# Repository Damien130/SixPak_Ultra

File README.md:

# SixPak_Ultra
- Currently in Alpha

A combination expansion card for the XT Bus, contains
  
  High speed Intel 16550 UART
  
  SVGA Controller
  
  Ethernet Controller
  
  AdLib compatible sound card
  
  Real Time Clock
  
  Floppy Controller with 3.5 Inch HD diskette support
  
This is a spiritual successor of AST's SixPak Plus ;)

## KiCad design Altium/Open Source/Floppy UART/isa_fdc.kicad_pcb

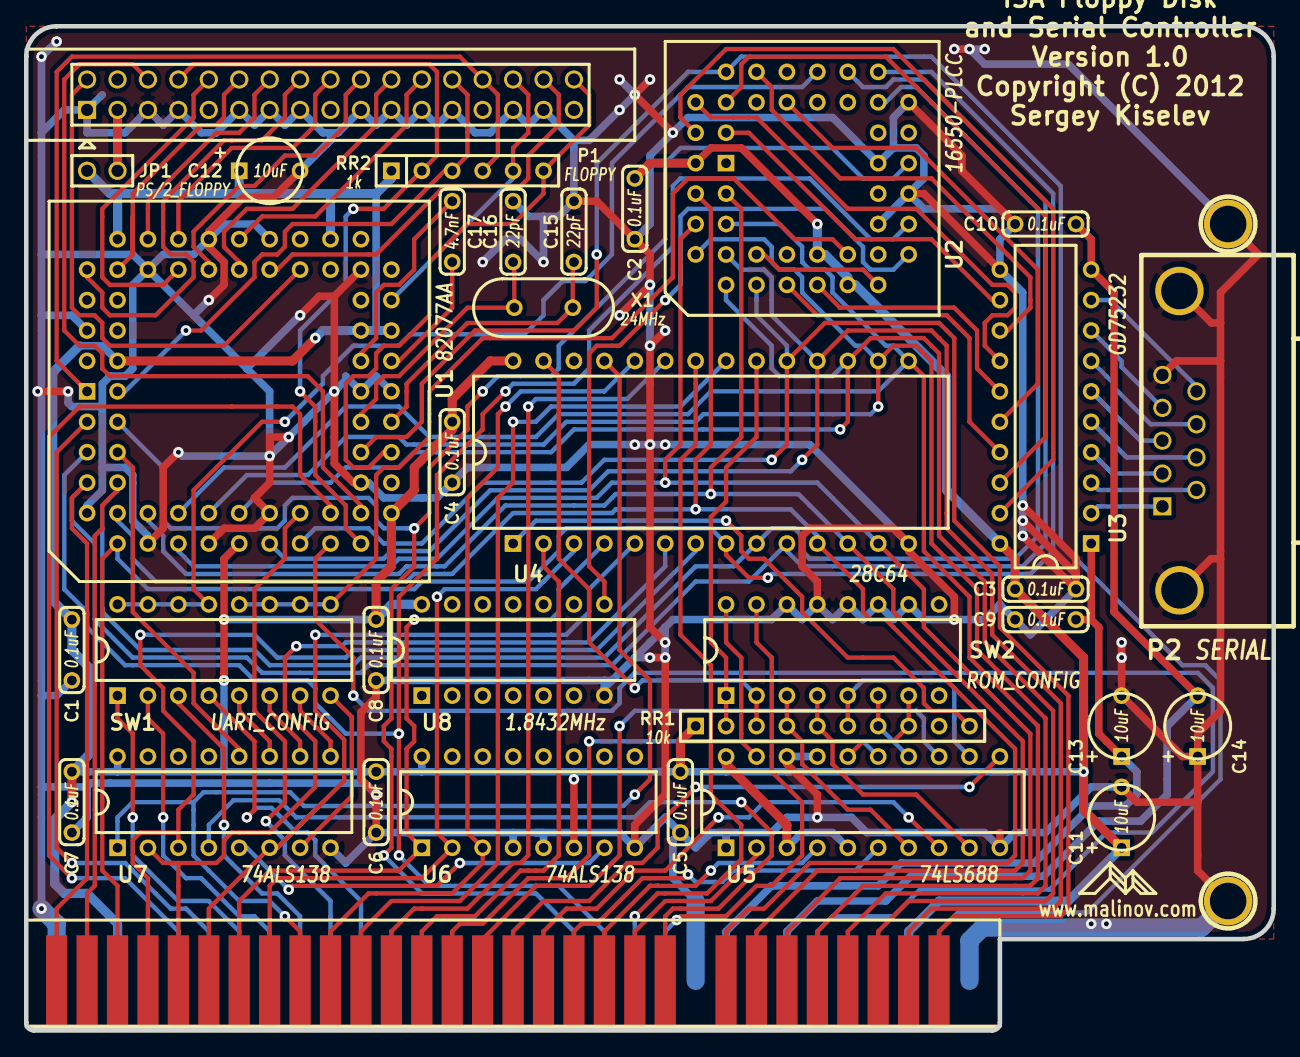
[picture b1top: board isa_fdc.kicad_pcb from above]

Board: 2 copper layers, 104.1 x 83.8 mm, 36 parts (0 on the bottom side), 102 nets.

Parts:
BUS1: BUSPC_DEV; Conn_Bus_ISA8
C1, C2, C3, C4, C5, C6, C7, C8, C9, C10: 0.1uF; Cap_Cer_504
C11, C12, C13, C14: 10uF; Cap_Tant_504
C15, C16: 22pF; Cap_Cer_504
C17: 4.7nF; Cap_Cer_504
HOLE1, HOLE2: CONN_1; HOLE_3MM
JP1: PS/2_FLOPPY; Conn_Pin_Header_2x1_Nokey
P1: FLOPPY; Conn_Pin_Header_17x2_Shroud
P2: SERIAL; Conn_Dsub_DE9M
RR1: 10k; Conn_SIL-10
RR2: 1k; Conn_SIL-6
SW1: UART_CONFIG; DIP16_300
SW2: ROM_CONFIG; DIP16_300
U1: 82077AA; PLCC68_TH
U2: 16550-PLCC; PLCC44_TH
U3: GD75232; DIP20_300
U4: 28C64; DIP28_600
U5: 74LS688; DIP20_300
U6, U7: 74ALS138; DIP16_300
U8: 1.8432MHz; DIP14_300
X1: 24MHz; Crystal_HC-49U_Vert

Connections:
/0x2E8: SW1.5, U7.11
/0x2F8: SW1.7, U7.9
/0x3E8: SW1.6, U7.10
/0x3F8: SW1.8, U7.7
/A0: BUS1.62, U1.7, U2.31, U4.10
/A1: BUS1.61, U1.8, U2.30, U4.9
/A2: BUS1.60, U1.10, U2.29, U4.8
/A3: BUS1.59, U4.7, U7.3
/A4: BUS1.58, U4.6, U7.2
/A5: BUS1.57, U4.5, U7.6
/A6: BUS1.56, U4.4, U6.1
/A7: BUS1.55, U4.3, U6.2
/A8: BUS1.54, U4.25, U7.1
/A9: BUS1.53, U4.24, U6.3
/A10: BUS1.52, U4.21
/A11: BUS1.51, U4.23
/A12: BUS1.50, U4.2
/A13: BUS1.49, U5.15
/A14: BUS1.48, U5.13
/A15: BUS1.47, U5.11
/A16: BUS1.46, U5.8
/A17: BUS1.45, U5.6
/A18: BUS1.44, U5.4
/A19: BUS1.43, U5.2
/AEN: BUS1.42, U7.4
/CTS: P2.8, U3.7
/D0: BUS1.40, U1.11, U2.2, U4.11
/D1: BUS1.39, U1.13, U2.3, U4.12
/D2: BUS1.38, U1.14, U2.4, U4.13
/D3: BUS1.37, U1.15, U2.5, U4.15
/D4: BUS1.36, U1.17, U2.6, U4.16
/D5: BUS1.35, U1.19, U2.7, U4.17
/D6: BUS1.34, U1.20, U2.8, U4.18
/D7: BUS1.33, U1.22, U2.9, U4.19
/DCD: P2.1, U3.2
/DENSL: P1.2, U1.49
/DIR: P1.18, U1.56
/DRQ2: BUS1.6, U1.24
/DSA: P1.14, U1.58
/DSB: P1.12, U1.62
/DSKCG: P1.34, RR2.6, U1.31
/DSR: P2.6, U3.3
/DTR: P2.4, U3.8
/FLOPPY_VCC: JP1.2, P1.3
/HDSEL: P1.32, U1.51
/INDEX: P1.8, RR2.2, U1.26
/IRQ3: BUS1.25, SW1.1
/IRQ4: BUS1.24, SW1.2
/IRQ5: BUS1.23, SW1.3
/IRQ6: BUS1.22, U1.23
/IRQ7: BUS1.21, SW1.4
/MEA: P1.10, U1.57
/MEB: P1.16, U1.61
/RDATA: P1.30, RR2.5, U1.41
/RDY/~BUSY: RR1.10, U4.1
/RESETDRV: BUS1.2, U1.32, U2.39
/RI: P2.9, U3.9
/RTS: P2.7, U3.5
/RX: P2.2, U3.4
/SIN: U2.11, U3.17
/SOUT: U2.13, U3.15
/STEP: P1.20, U1.55
/TC: BUS1.27, U1.25
/TRK00: P1.26, RR2.3, U1.2
/TX: P2.3, U3.6
/UART_IRQ: SW1.13, SW1.14, SW1.15, SW1.16, U2.33
/WDATA: P1.22, U1.53
/WE: P1.24, U1.52
/WP: P1.28, RR2.4, U1.1
/~CTS: U2.40, U3.14
/~DACK2: BUS1.26, U1.3
/~DCD: U2.42, U3.19
/~DSR: U2.41, U3.18
/~DTR: U2.37, U3.13
/~FDC_CS: U1.6, U7.12
/~IOR: BUS1.14, U1.4, U2.24
/~IOW: BUS1.13, U1.5, U2.20
/~MEMR: BUS1.12, U4.22
/~MEMW: BUS1.11, SW2.15
/~RI: U2.43, U3.12
/~ROMW: RR1.3, SW2.2, U4.27
/~ROM_CS_IN: SW2.16, U5.19
/~ROM_CS: RR1.2, SW2.1, U4.20
/~RTS: U2.36, U3.16
/~UART_CS: SW1.9, SW1.10, SW1.11, SW1.12, U2.16
GND: BUS1.1, BUS1.10, BUS1.31, C1.2, C2.2, C3.2, C4.2, C5.2, C6.2, C7.2, C8.2, C9.2, C10.1, C11.2, C12.2, C13.2, C14.1, C15.2, C16.2, HOLE1.1, HOLE2.1, P1.1, P1.5, P1.7, P1.11, P1.13, P1.15, P1.19, P1.21, P1.23, P1.25, P1.29, P1.31, P2.5, SW2.10, SW2.11, SW2.12, SW2.13, SW2.14, U1.9, U1.12, U1.16, U1.21, U1.30, U1.35, U1.36, U1.45, U1.50, U1.54, U1.59, U1.65, U2.21, U2.22, U2.25, U2.28, U3.11, U4.14, U5.1, U5.10, U5.17, U5.18, U6.4, U6.5, U6.8, U7.8, U8.7
unnamed: U2.10, U2.17
unnamed: RR1.7, SW2.6, U5.14
unnamed: RR1.5, SW2.4, U5.9
unnamed: RR1.8, SW2.7, U5.16
unnamed: U6.7, U7.5
unnamed: C17.2, U1.37
unnamed: C17.1, U1.38
unnamed: C16.1, U1.34, X1.2
unnamed: P1.6, U1.28
unnamed: U2.18, U8.8
unnamed: C15.1, U1.33, X1.1
unnamed: RR1.6, SW2.5, U5.12
unnamed: RR1.4, SW2.3, U5.7
VCC: BUS1.3, BUS1.29, C1.1, C2.1, C3.1, C4.1, C5.1, C6.1, C7.1, C8.1, C11.1, C12.1, JP1.1, RR1.1, RR2.1, U1.18, U1.27, U1.39, U1.40, U1.46, U1.60, U1.68, U2.14, U2.15, U2.44, U3.20, U4.28, U5.3, U5.5, U5.20, U6.6, U6.16, U7.16, U8.14
VDD: BUS1.9, C9.1, C13.1, U3.1
VSS: BUS1.7, C10.2, C14.2, U3.10

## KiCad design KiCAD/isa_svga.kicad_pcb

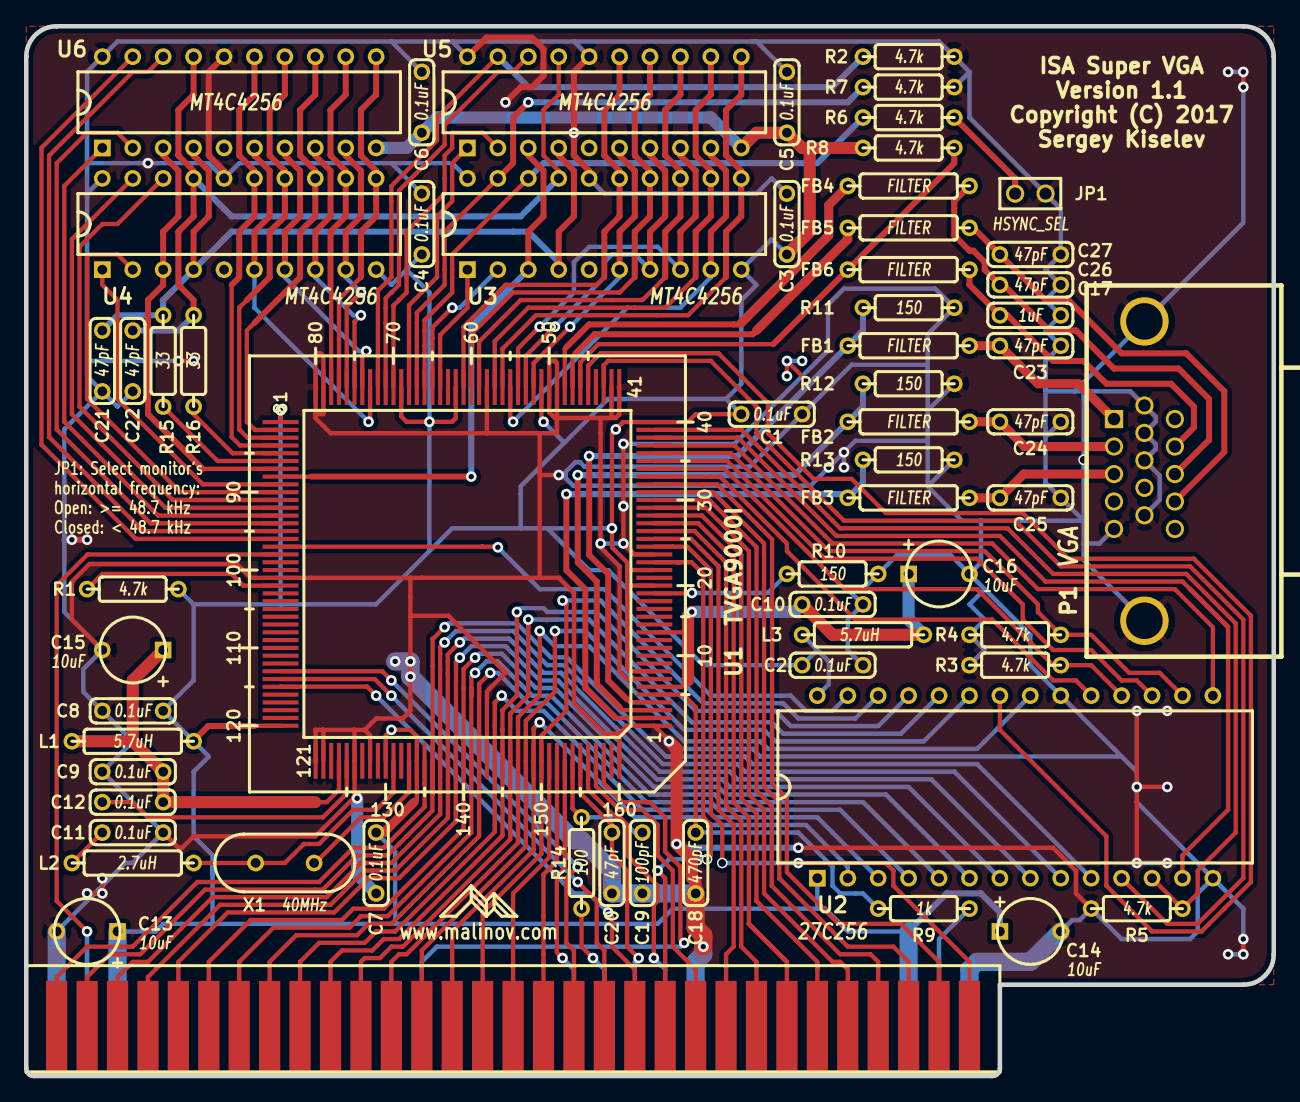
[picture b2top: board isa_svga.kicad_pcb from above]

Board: 2 copper layers, 104.1 x 87.6 mm, 62 parts (0 on the bottom side), 113 nets.

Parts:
BUS1: BUSPC_DEV; Conn_Bus_ISA8
C1, C2, C3, C4, C5, C6, C7, C8, C9, C10, C11, C12: 0.1uF; Cap_Cer_504
C13, C14, C15, C16: 10uF; Cap_Tant_504
C17: 1uF; Cap_Cer_504
C18: 470pF; Cap_Cer_504
C19: 100pF; Cap_Cer_504
C20, C21, C22, C23, C24, C25, C26, C27: 47pF; Cap_Cer_504
FB1, FB2, FB3, FB4, FB5, FB6: FILTER; Res_1016
JP1: HSYNC_SEL; Conn_Pin_Header_2x1_Nokey
L1, L3: 5.7uH; Res_1016
L2: 2.7uH; Res_1016
P1: VGA; Conn_Dsub_DE15F
R1, R2, R3, R4, R5, R6, R7, R8: 4.7k; Res_762
R9: 1k; Res_762
R10, R11, R12, R13: 150; Res_762
R14: 100; Res_762
R15, R16: 33; Res_762
U1: TVGA9000I; PQFP-160
U2: 27C256; DIP28_600
U3, U4, U5, U6: MT4C4256; DIP20_300
X1: 40MHz; Crystal_HC-49U_Vert

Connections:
/A0: BUS1.62, U1.135
/A1: BUS1.61, U1.136, U2.10
/A2: BUS1.60, U1.137, U2.9
/A3: BUS1.59, U1.138, U2.8
/A4: BUS1.58, U1.139, U2.7
/A5: BUS1.57, U1.140, U2.6
/A6: BUS1.56, U1.141, U2.5
/A7: BUS1.55, U1.142, U2.4
/A8: BUS1.54, U1.144, U2.3
/A9: BUS1.53, U1.145, U2.25
/A10: BUS1.52, U1.146, U2.24
/A11: BUS1.51, U1.147, U2.21
/A12: BUS1.50, U1.148, U2.23
/A13: BUS1.49, U1.149, U2.2
/A14: BUS1.48, U1.150, U2.26
/A15: BUS1.47, U1.151
/A16: BUS1.46, U1.152
/A17: BUS1.45, U1.113
/A18: BUS1.44, U1.114
/A19: BUS1.43, U1.115
/AEN: BUS1.42, U1.22
/AVDD1: C9.1, C12.1, C15.1, L1.2, U1.124
/AVDD2: C10.1, C16.1, L3.2, U1.6, U1.13
/B: FB3.1, R13.1, U1.2
/BLUE: C25.1, FB3.2, P1.3
/D0: BUS1.40, U1.25
/D1: BUS1.39, U1.26
/D2: BUS1.38, U1.27
/D3: BUS1.37, U1.28
/D4: BUS1.36, U1.29
/D5: BUS1.35, U1.30
/D6: BUS1.34, U1.31
/D7: BUS1.33, U1.32
/G: FB2.1, R12.1, U1.3
/GREEN: C24.1, FB2.2, P1.2
/HSYNC: FB4.2, U1.48
/IOCHRDY: BUS1.41, U1.157
/MAA0: U1.52, U3.6, U5.6
/MAA1: U1.53, U3.7, U5.7
/MAA2: U1.54, U3.8, U5.8
/MAA3: U1.55, U3.9, U5.9
/MAA4: U1.56, U3.11, U5.11
/MAA5: U1.57, U3.12, U5.12
/MAA6: U1.59, U3.13, U5.13
/MAA7: U1.60, U3.14, U5.14
/MAA8: U1.61, U3.15, U5.15
/MAB0: U1.73, U4.6, U6.6
/MAB1: U1.74, U4.7, U6.7
/MAB2: U1.75, U4.8, U6.8
/MAB3: U1.76, U4.9, U6.9
/MAB4: U1.77, U4.11, U6.11
/MAB5: U1.78, U4.12, U6.12
/MAB6: U1.82, U4.13, U6.13
/MAB7: U1.83, U4.14, U6.14
/MAB8: U1.84, U4.15, U6.15
/MD0: U1.64, U3.1
/MD1: U1.65, U3.2
/MD2: R6.1, U1.66, U3.18
/MD3: R7.1, U1.67, U3.19
/MD4: U1.68, U5.1
/MD5: U1.70, U5.2
/MD6: U1.71, U5.18
/MD7: R2.1, U1.72, U5.19
/MD16: U1.89, U4.1
/MD17: U1.90, U4.2
/MD18: U1.91, U4.18
/MD19: U1.92, U4.19
/MD20: U1.93, U6.1
/MD21: U1.94, U6.2
/MD22: U1.95, U6.18
/MD23: U1.96, U6.19
/MONITOR: FB6.2, R8.1, U1.46
/OSC: BUS1.30, U1.98
/R: FB1.1, R11.1, U1.4
/RED: C23.1, FB1.2, P1.1
/RESET: BUS1.2, R9.1
/RMD0: U1.43, U2.11
/RMD1: R5.1, U1.39, U2.12
/RMD2: U1.38, U2.13
/RMD3: U1.37, U2.15
/RMD4: R4.1, U1.36, U2.16
/RMD5: U1.35, U2.17
/RMD6: R3.1, U1.34, U2.18
/RMD7: U1.33, U2.19
/ROMA0: U1.97, U2.27
/VSYNC: FB5.2, U1.47
/~CAS: C22.1, R16.2, U3.17, U4.17, U5.17, U6.17
/~IOR: BUS1.14, U1.153
/~IOW: BUS1.13, R14.1
/~MEMR: BUS1.12, C20.1, U1.155
/~MEMW: BUS1.11, U1.156
/~NMI: BUS1.32, U1.24
/~RAS: C21.1, R15.2, U3.4, U4.4, U5.4, U6.4
/~REFRESH: BUS1.19, U1.158
/~ROMCS: U1.45, U2.22
/~WE0: U1.88, U3.3, U5.3
/~WE2: U1.87, U4.3, U6.3
GND: BUS1.1, BUS1.10, BUS1.31, C1.2, C2.2, C3.2, C4.2, C5.2, C6.2, C7.2, C8.2, C9.2, C10.2, C11.2, C13.2, C14.2, C15.2, C16.2, C17.2, C18.2, C19.2, C20.2, C21.2, C22.2, C23.2, C24.2, C25.2, C26.2, C27.2, JP1.2, P1.5, P1.6, P1.7, P1.8, P1.10, R2.2, R3.2, R4.2, R5.2, R7.2, R10.2, R11.2, R12.2, R13.2, U1.1, U1.7, U1.23, U1.41, U1.42, U1.49, U1.50, U1.58, U1.79, U1.80, U1.101, U1.121, U1.122, U1.126, U1.128, U1.143, U1.160, U2.14, U2.20, U3.16, U3.20, U4.16, U4.20, U5.16, U5.20, U6.16, U6.20
unnamed: C11.1, L2.1
unnamed: C12.2, U1.125
unnamed: C17.1, FB6.1, P1.12
unnamed: C18.1, R9.2, U1.5
unnamed: C19.1, R14.2, U1.154
unnamed: C26.1, FB4.1, P1.13
unnamed: C27.1, FB5.1, P1.14
unnamed: JP1.1, R6.2
unnamed: L2.2, U1.131, X1.2
unnamed: R1.1, U1.102
unnamed: R10.1, U1.18
unnamed: R15.1, U1.86
unnamed: R16.1, U1.85
unnamed: U1.133, X1.1
VCC: BUS1.3, BUS1.29, C1.1, C2.1, C3.1, C4.1, C5.1, C6.1, C7.1, C8.1, C13.1, C14.1, L1.1, L3.1, R1.2, R8.2, U1.8, U1.19, U1.21, U1.40, U1.51, U1.62, U1.69, U1.81, U1.120, U1.130, U1.134, U2.1, U2.28, U3.10, U4.10, U5.10, U6.10

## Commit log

2022-10-26 add Altium Schematic
2022-10-26 Added Design library
2022-10-26 Added Footprint for TVGA9000
2022-10-26 added files
2022-10-28 proposal
2022-10-28 modified directory structure
2022-10-28 Renamed Project
2022-10-28 Oct. 27 checkoff
2022-10-29 Finished VGA portion - Oct 28 checkoff
2022-10-30 finished proposal
2022-10-31 Oct 31 Wrap-Up. - UART
2022-10-31 Oct 31 Wrap Up - UART
2022-10-31 added UART serial port + res array
2022-11-21 brought up to date
2022-11-22 finalized board outline, UART, Floppy and VGA portion
2022-11-22 Finished AdLib schematic
2022-11-23 all SIX functions for the SIXPAK Ultra is now implemented.
2022-11-24 Finished Schematic and SVGA + Adlib processing portion PC board design.
2022-11-24 adding additional project files
2022-11-30 Completed PCB placement
2022-11-30 Before routing
2022-11-30 Before route
2022-11-30 Fixed spacing
2022-11-30 Rearranged
2022-12-02 before routing, with bus routed
2022-12-07 Completed PCB routing, starting final schematic check.
2022-12-07 Project Completed. Added initial gerber output in output folder.

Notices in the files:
Altium/Open Source/Floppy UART/isa_fdc.kicad_pcb:
Copyright (C) 2012
KiCAD/isa_svga.kicad_pcb:
Copyright (C) 2017
